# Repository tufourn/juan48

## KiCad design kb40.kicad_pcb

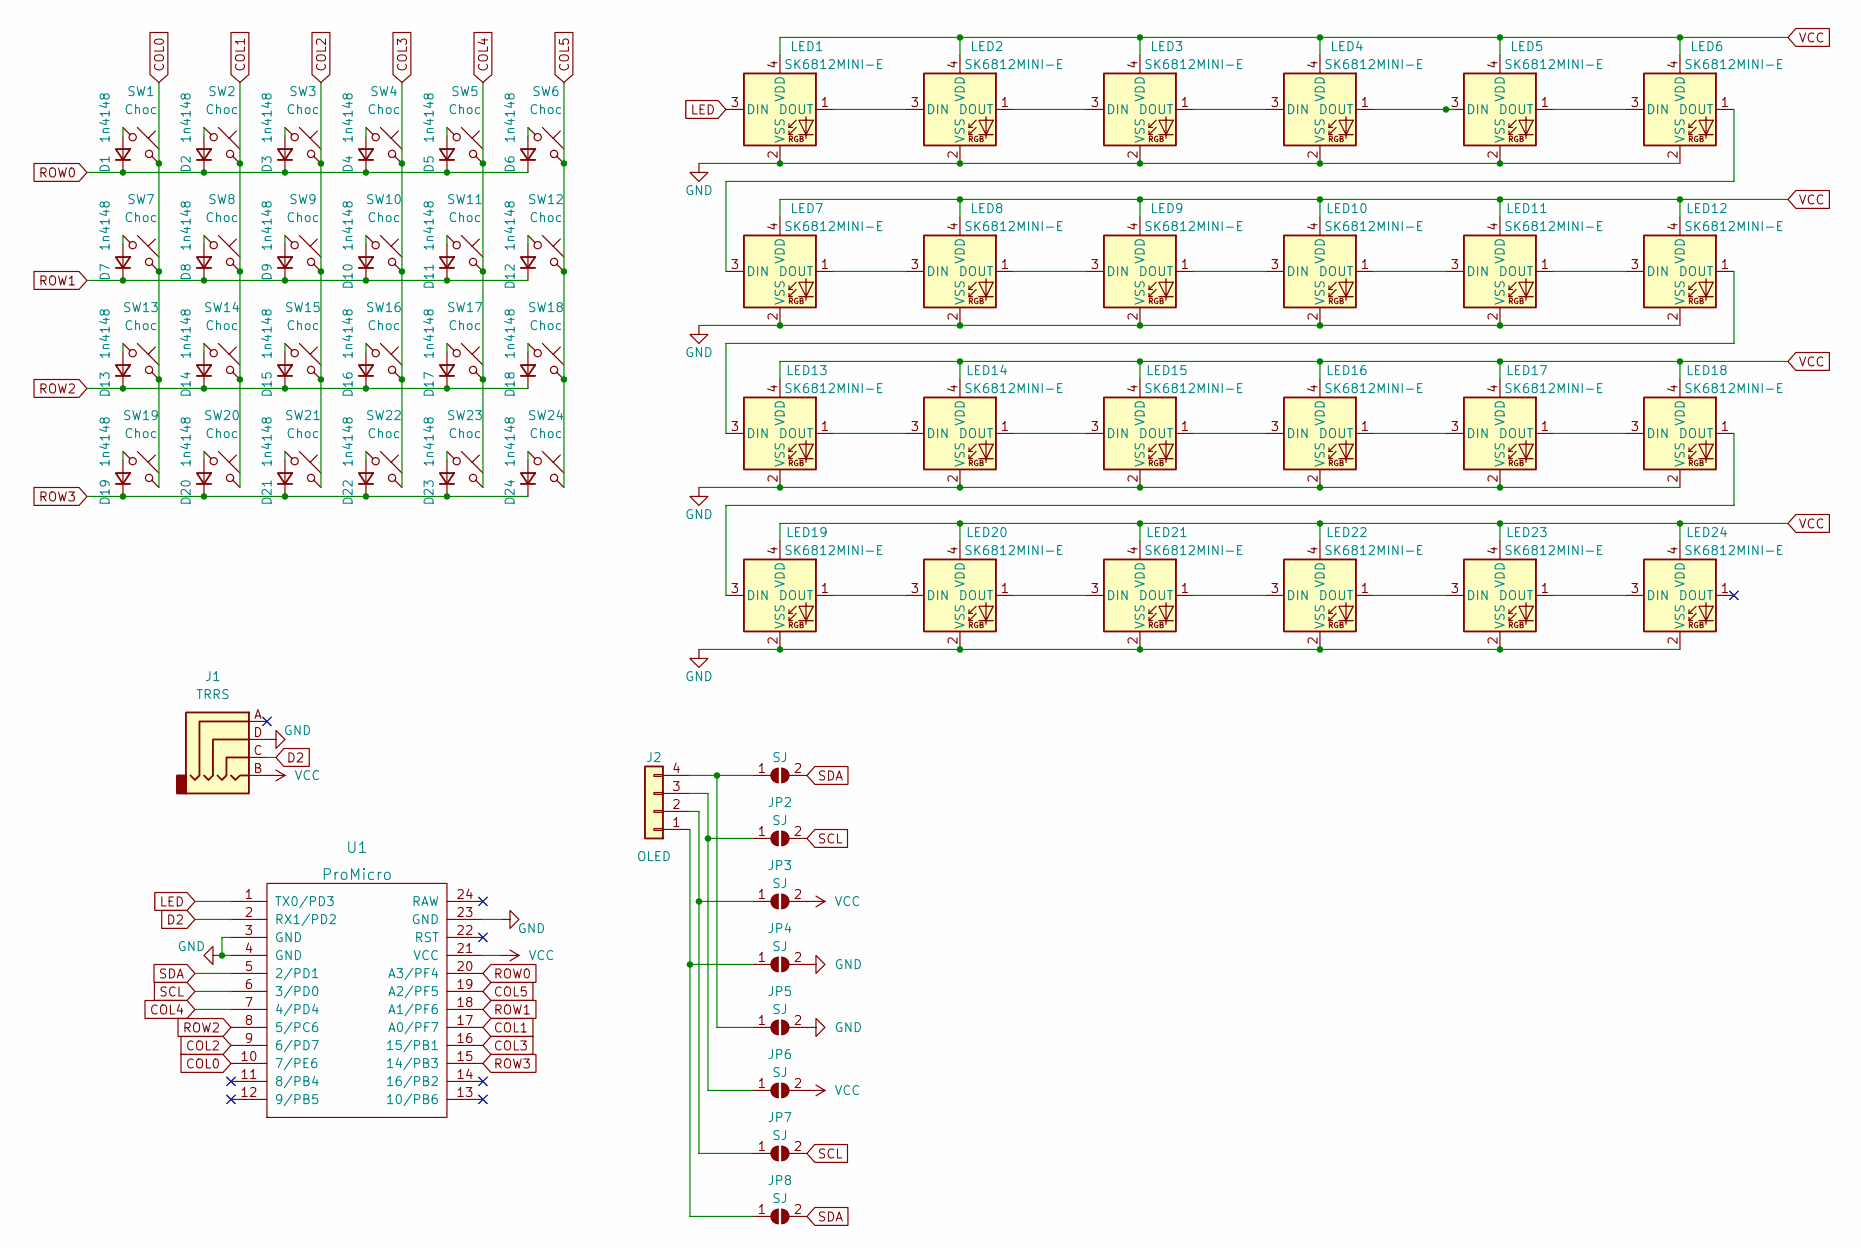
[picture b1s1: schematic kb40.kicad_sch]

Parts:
D1, D2, D3, D4, D5, D6, D7, D8, D9, D10, D11, D12, D13, D14, D15, D16, D17, D18, D19, D20, D21, D22, D23, D24: 1n4148; D_SOD-123
J1: TRRS; PJ-320A
J2: OLED; PinSocket_1x04_P2.54mm_Vertical
JP1, JP2, JP3, JP4, JP5, JP6, JP7, JP8: SJ; SolderJumper-2_P1.3mm_Open_TrianglePad1.0x1.5mm
LED1, LED2, LED3, LED4, LED5, LED6, LED7, LED8, LED9, LED10, LED11, LED12, LED13, LED14, LED15, LED16, LED17, LED18, LED19, LED20, LED21, LED22, LED23, LED24: SK6812MINI-E; SK6812-MINI-E
SW1, SW2, SW3, SW4, SW5, SW6, SW7, SW8, SW9, SW10, SW11, SW12, SW13, SW14, SW15, SW16, SW17, SW18, SW19, SW20, SW21, SW22, SW23, SW24: Choc; Kailh_socket_PG1350_reversible
U1: ProMicro; ArduinoProMicro-BackSide

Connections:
COL0: SW1.2, SW7.2, SW13.2, SW19.2, U1.10 (7/PE6)
COL1: SW2.2, SW8.2, SW14.2, SW20.2, U1.17 (A0/PF7)
COL2: SW3.2, SW9.2, SW15.2, SW21.2, U1.9 (6/PD7)
COL3: SW4.2, SW10.2, SW16.2, SW22.2, U1.16 (15/PB1)
COL4: SW5.2, SW11.2, SW17.2, SW23.2, U1.7 (4/PD4)
COL5: SW6.2, SW12.2, SW18.2, SW24.2, U1.19 (A2/PF5)
D2: J1.C, U1.2 (RX1/PD2)
GND: J1.D, JP4.2 (B), JP5.2 (B), LED1.2 (VSS), LED2.2 (VSS), LED3.2 (VSS), LED4.2 (VSS), LED5.2 (VSS), LED6.2 (VSS), LED7.2 (VSS), LED8.2 (VSS), LED9.2 (VSS), LED10.2 (VSS), LED11.2 (VSS), LED12.2 (VSS), LED13.2 (VSS), LED14.2 (VSS), LED15.2 (VSS), LED16.2 (VSS), LED17.2 (VSS), LED18.2 (VSS), LED19.2 (VSS), LED20.2 (VSS), LED21.2 (VSS), LED22.2 (VSS), LED23.2 (VSS), LED24.2 (VSS), U1.3 (GND), U1.4 (GND), U1.23 (GND)
LED: LED1.3 (DIN), U1.1 (TX0/PD3)
unnamed: D1.2 (A), SW1.1
unnamed: D2.2 (A), SW2.1
unnamed: D3.2 (A), SW3.1
unnamed: D4.2 (A), SW4.1
unnamed: D5.2 (A), SW5.1
unnamed: D6.2 (A), SW6.1
unnamed: D7.2 (A), SW7.1
unnamed: D8.2 (A), SW8.1
unnamed: D9.2 (A), SW9.1
unnamed: D10.2 (A), SW10.1
unnamed: D11.2 (A), SW11.1
unnamed: D12.2 (A), SW12.1
unnamed: D13.2 (A), SW13.1
unnamed: D14.2 (A), SW14.1
unnamed: D15.2 (A), SW15.1
unnamed: D16.2 (A), SW16.1
unnamed: D17.2 (A), SW17.1
unnamed: D18.2 (A), SW18.1
unnamed: D19.2 (A), SW19.1
unnamed: D20.2 (A), SW20.1
unnamed: D21.2 (A), SW21.1
unnamed: D22.2 (A), SW22.1
unnamed: D23.2 (A), SW23.1
unnamed: D24.2 (A), SW24.1
unnamed: J2.1, JP4.1 (A), JP8.1 (A)
unnamed: J2.2, JP3.1 (A), JP7.1 (A)
unnamed: J2.3, JP2.1 (A), JP6.1 (A)
unnamed: J2.4, JP1.1 (A), JP5.1 (A)
unnamed: LED1.1 (DOUT), LED2.3 (DIN)
unnamed: LED2.1 (DOUT), LED3.3 (DIN)
unnamed: LED3.1 (DOUT), LED4.3 (DIN)
unnamed: LED4.1 (DOUT), LED5.3 (DIN)
unnamed: LED5.1 (DOUT), LED6.3 (DIN)
unnamed: LED6.1 (DOUT), LED7.3 (DIN)
unnamed: LED7.1 (DOUT), LED8.3 (DIN)
unnamed: LED8.1 (DOUT), LED9.3 (DIN)
unnamed: LED10.1 (DOUT), LED11.3 (DIN)
unnamed: LED9.1 (DOUT), LED10.3 (DIN)
unnamed: LED11.1 (DOUT), LED12.3 (DIN)
unnamed: LED12.1 (DOUT), LED13.3 (DIN)
unnamed: LED13.1 (DOUT), LED14.3 (DIN)
unnamed: LED14.1 (DOUT), LED15.3 (DIN)
unnamed: LED15.1 (DOUT), LED16.3 (DIN)
unnamed: LED16.1 (DOUT), LED17.3 (DIN)
unnamed: LED17.1 (DOUT), LED18.3 (DIN)
unnamed: LED18.1 (DOUT), LED19.3 (DIN)
unnamed: LED19.1 (DOUT), LED20.3 (DIN)
unnamed: LED20.1 (DOUT), LED21.3 (DIN)
unnamed: LED21.1 (DOUT), LED22.3 (DIN)
unnamed: LED22.1 (DOUT), LED23.3 (DIN)
unnamed: LED23.1 (DOUT), LED24.3 (DIN)
ROW0: D1.1 (K), D2.1 (K), D3.1 (K), D4.1 (K), D5.1 (K), D6.1 (K), U1.20 (A3/PF4)
ROW1: D7.1 (K), D8.1 (K), D9.1 (K), D10.1 (K), D11.1 (K), D12.1 (K), U1.18 (A1/PF6)
ROW2: D13.1 (K), D14.1 (K), D15.1 (K), D16.1 (K), D17.1 (K), D18.1 (K), U1.8 (5/PC6)
ROW3: D19.1 (K), D20.1 (K), D21.1 (K), D22.1 (K), D23.1 (K), D24.1 (K), U1.15 (14/PB3)
SCL: JP2.2 (B), JP7.2 (B), U1.6 (3/PD0)
SDA: JP1.2 (B), JP8.2 (B), U1.5 (2/PD1)
VCC: J1.B, JP3.2 (B), JP6.2 (B), LED1.4 (VDD), LED2.4 (VDD), LED3.4 (VDD), LED4.4 (VDD), LED5.4 (VDD), LED6.4 (VDD), LED7.4 (VDD), LED8.4 (VDD), LED9.4 (VDD), LED10.4 (VDD), LED11.4 (VDD), LED12.4 (VDD), LED13.4 (VDD), LED14.4 (VDD), LED15.4 (VDD), LED16.4 (VDD), LED17.4 (VDD), LED18.4 (VDD), LED19.4 (VDD), LED20.4 (VDD), LED21.4 (VDD), LED22.4 (VDD), LED23.4 (VDD), LED24.4 (VDD), U1.21 (VCC)

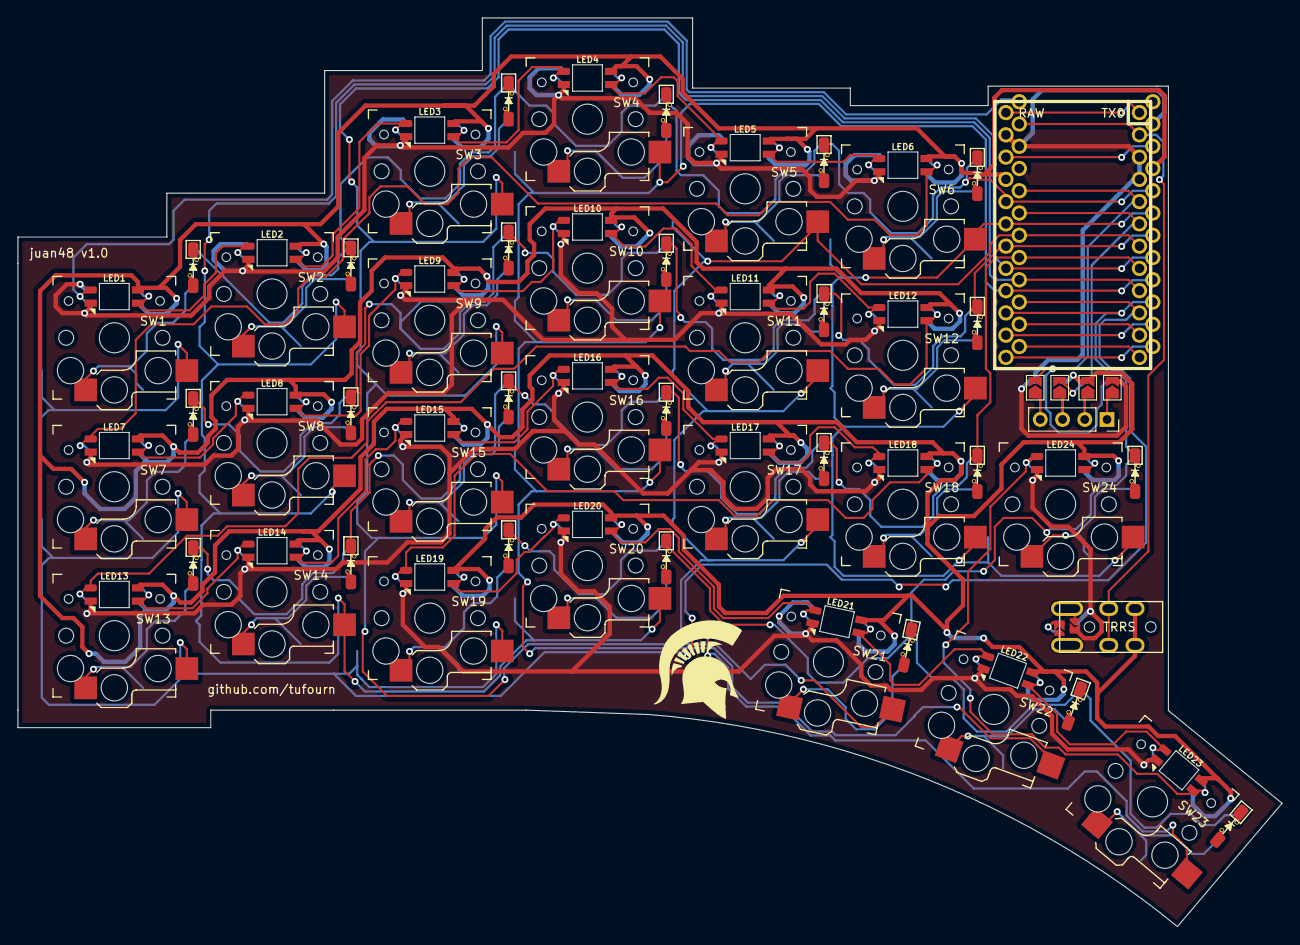
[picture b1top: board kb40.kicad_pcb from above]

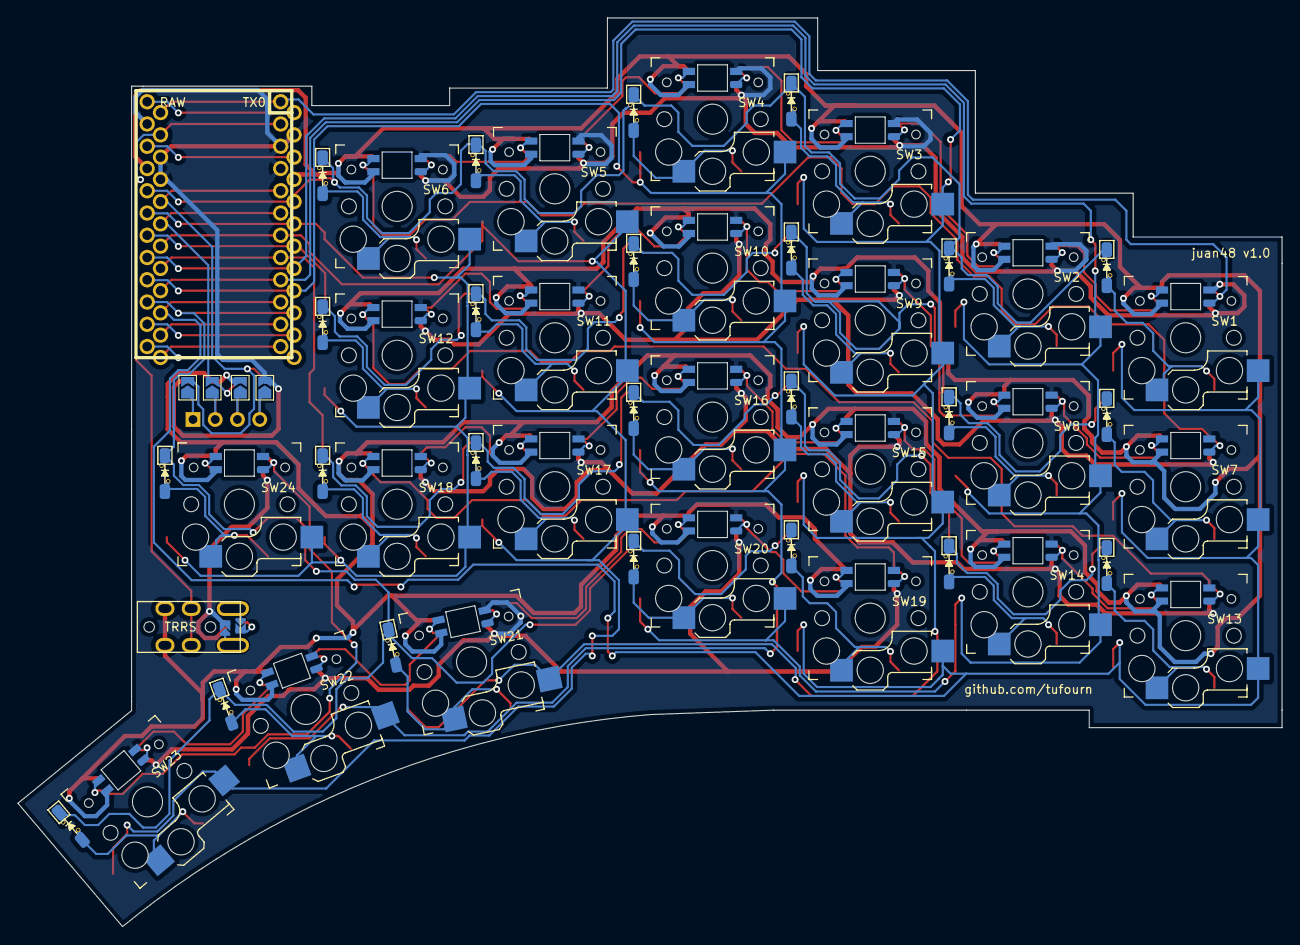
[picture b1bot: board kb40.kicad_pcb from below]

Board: 2 copper layers, 144.3 x 103.7 mm, 83 parts (4 on the bottom side), 67 nets.

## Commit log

2023-02-17 initial schematic
2023-02-17 initial layout
2023-02-17 generate test step file
2023-02-18 initial matrix routing
2023-02-22 initial rgb routing
2023-02-22 initial completed routing
2023-02-22 added silkscreen
2023-02-22 fix i2c and generate gerbers
